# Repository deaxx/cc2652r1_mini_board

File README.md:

# cc2652r_board
This is final version.

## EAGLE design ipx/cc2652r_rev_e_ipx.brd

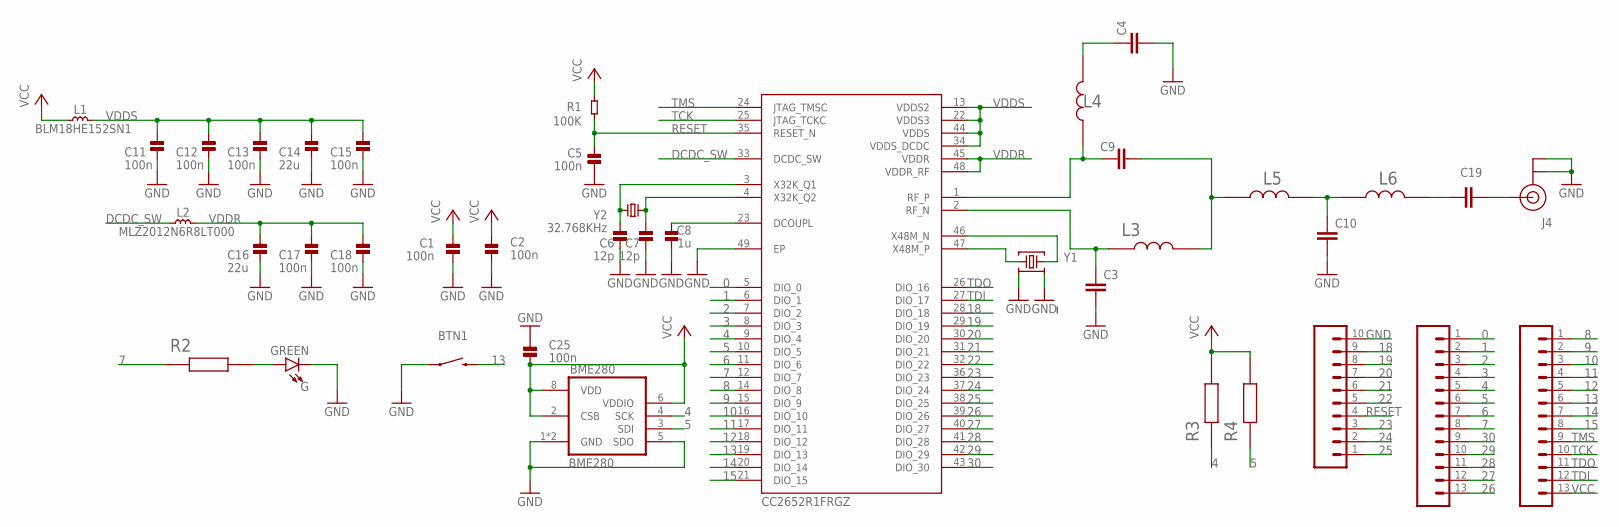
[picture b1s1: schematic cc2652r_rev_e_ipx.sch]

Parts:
BME280: BME280
BTN1: MOMENTARY-SWITCH-SPST-SMD-4.6X2.8MM; TACTILE_SWITCH_SMD_4.6X2.8MM
C1, C2, C5, C11, C12, C13, C15, C17, C18, C25: 100n; _PKG_C_0402
C3, C9, C10: 1pF; CAPC1005X40N
C4, C19: 12pF; CAPC1005X40N
C6, C7: 12p; _PKG_C_0402
C8: 1u; _PKG_C_0402
C14, C16: 22u; _PKG_C_0805
G: GREEN; LED-0603
IC3: CC2652R1FRGZ; QFN50P700X700X100-49N
J1, J2: CONN_051.27MM; 1X05_1.27MM
J3: CONN_061.27MM; 1X06_1.27MM
J4: U.FL
L1: BLM18HE152SN1; _PKG_L_0603
L2: MLZ2012N6R8LT000; _PKG_C_0805
L3, L4: 2.4nH; INDC1005X40N
L5, L6: 2nH; INDC1005X40N
R1: 100K; _PKG_C_0402
R2: 2.2k; RESC1005X40N
R3, R4: 4.7k; RESC1005X40N
Y1: Q22FA12800150; XTAL-4P-2016
Y2: 32.768KHz; XTAL-2P-3215

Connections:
0: IC3.5 (DIO_0), J1.1
1: IC3.6 (DIO_1), J1.2
2: IC3.7 (DIO_2), J1.3
3: IC3.8 (DIO_3), J1.4
4: BME280.4 (SCK), IC3.9 (DIO_4), J1.5, R3.1
5: BME280.3 (SDI), IC3.10 (DIO_5), J1.6, R4.1
6: IC3.11 (DIO_6), J1.7
7: IC3.12 (DIO_7), J1.8, R2.1
8: IC3.14 (DIO_8), J2.1
9: IC3.15 (DIO_9), J2.2
10: IC3.16 (DIO_10), J2.3
11: IC3.17 (DIO_11), J2.4
12: IC3.18 (DIO_12), J2.5
13: BTN1.3 (2), BTN1.4 (2), IC3.19 (DIO_13), J2.6
14: IC3.20 (DIO_14), J2.7
15: IC3.21 (DIO_15), J2.8
18: IC3.28 (DIO_18), J3.9
19: IC3.29 (DIO_19), J3.8
20: IC3.30 (DIO_20), J3.7
21: IC3.31 (DIO_21), J3.6
22: IC3.32 (DIO_22), J3.5
23: IC3.36 (DIO_23), J3.3
24: IC3.37 (DIO_24), J3.2
25: IC3.38 (DIO_25), J3.1
26: IC3.39 (DIO_26), J1.13
27: IC3.40 (DIO_27), J1.12
28: IC3.41 (DIO_28), J1.11
29: IC3.42 (DIO_29), J1.10
30: IC3.43 (DIO_30), J1.9
DCDC_SW: IC3.33 (DCDC_SW), L2.1
DCOUPL: C8.2, IC3.23 (DCOUPL)
GND: BME280.1 (GND), BME280.5 (SDO), BME280.7 (GND), BTN1.1, BTN1.2 (1), C1.1, C2.1, C3.2, C4.2, C5.1, C6.1, C7.1, C8.1, C10.2, C11.2, C12.2, C13.2, C14.2, C15.2, C16.2, C17.2, C18.2, C25.2, G.C, IC3.49 (EP), J3.10, J4.1 (GND), J4.2 (GND), Y1.2, Y1.4
unnamed: C9.1, IC3.1 (RF_P), L4.1
unnamed: C3.1, IC3.2 (RF_N), L3.1
unnamed: C4.1, L4.2
unnamed: C9.2, L3.2, L5.1
unnamed: C19.1, L6.2
unnamed: G.A, R2.2
unnamed: C19.2, J4.FEED (SIGNAL)
unnamed: C10.1, L5.2, L6.1
RESET: C5.2, IC3.35 (RESET_N), J3.4, R1.1
TCK: IC3.25 (JTAG_TCKC), J2.10
TDI: IC3.27 (DIO_17), J2.12
TDO: IC3.26 (DIO_16), J2.11
TMS: IC3.24 (JTAG_TMSC), J2.9
VCC: BME280.2 (CSB), BME280.6 (VDDIO), BME280.8 (VDD), C1.2, C2.2, C25.1, J2.13, L1.1, R1.2, R3.2, R4.2
VDDR: C16.1, C17.1, C18.1, IC3.45 (VDDR), IC3.48 (VDDR_RF), L2.2
VDDS: C11.1, C12.1, C13.1, C14.1, C15.1, IC3.13 (VDDS2), IC3.22 (VDDS3), IC3.34 (VDDS_DCDC), IC3.44 (VDDS), L1.2
X32K_Q1: C6.2, IC3.3 (X32K_Q1), Y2.1
X32K_Q2: C7.2, IC3.4 (X32K_Q2), Y2.2
X48M_N: IC3.46 (X48M_N), Y1.3
X48M_P: IC3.47 (X48M_P), Y1.1

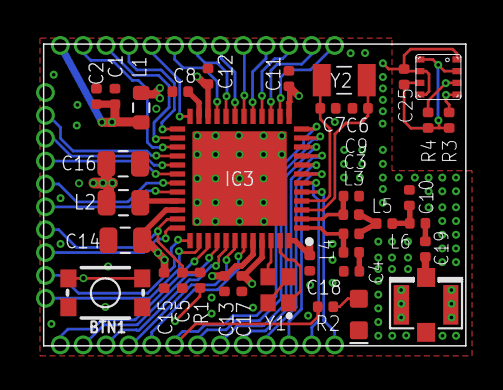
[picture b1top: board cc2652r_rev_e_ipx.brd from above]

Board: 4 copper layers, 23.5 x 16.8 mm, 40 parts (0 on the bottom side), 52 nets.

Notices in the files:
parts and their libraries:
SparkFun-Switches: Licensing: Creative Commons ShareAlike 4.0 International - https://creativecommons.org/licenses/by-sa/4.0
